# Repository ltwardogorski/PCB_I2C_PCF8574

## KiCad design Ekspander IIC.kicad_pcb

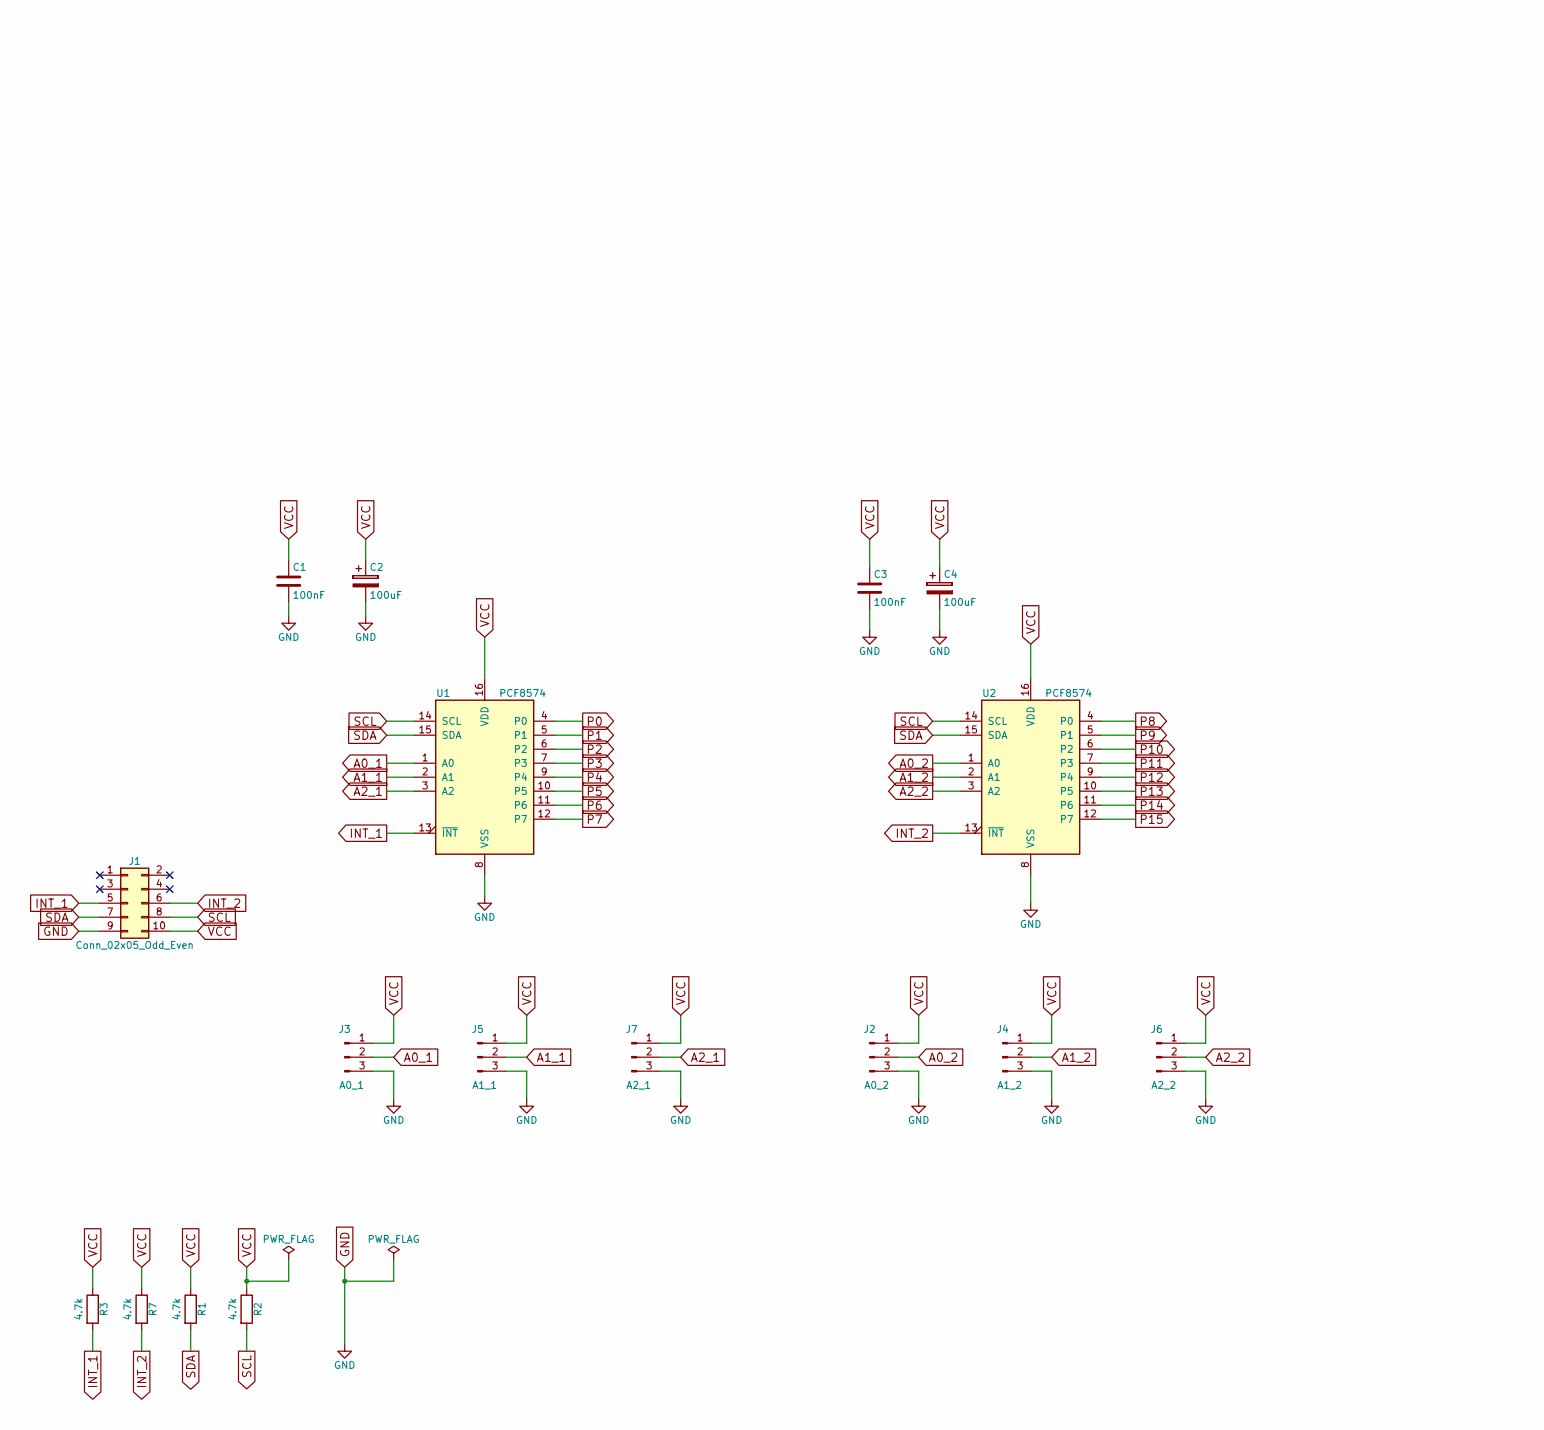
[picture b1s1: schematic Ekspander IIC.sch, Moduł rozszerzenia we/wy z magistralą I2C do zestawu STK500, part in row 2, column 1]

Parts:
C1, C3: 100nF; C_0805
C2, C4: 100uF; CP_Elec_8x6.5
J1: Conn_02x05_Odd_Even; Pin_Header_Straight_2x05_Pitch2.54mm
J2: A0_2; Pin_Header_Straight_1x03_Pitch2.54mm
J3: A0_1; Pin_Header_Straight_1x03_Pitch2.54mm
J4: A1_2; Pin_Header_Straight_1x03_Pitch2.54mm
J5: A1_1; Pin_Header_Straight_1x03_Pitch2.54mm
J6: A2_2; Pin_Header_Straight_1x03_Pitch2.54mm
J7: A2_1; Pin_Header_Straight_1x03_Pitch2.54mm
R1, R2, R3, R7: 4.7k; R_0805
U1, U2: PCF8574; DIP-16_W7.62mm

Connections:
A0_1: J3.2, U1.1 (A0)
A0_2: J2.2, U2.1 (A0)
A1_1: J5.2, U1.2 (A1)
A1_2: J4.2, U2.2 (A1)
A2_1: J7.2, U1.3 (A2)
A2_2: J6.2, U2.3 (A2)
GND: C1.2, C2.2, C3.2, C4.2, J1.9, J2.3, J3.3, J4.3, J5.3, J6.3, J7.3, U1.8 (VSS), U2.8 (VSS); also elsewhere on the board
INT_1: J1.5, R3.2, U1.13 (~INT~)
INT_2: J1.6, R7.2, U2.13 (~INT~)
P0: U1.4 (P0); also elsewhere on the board
P1: U1.5 (P1); also elsewhere on the board
P2: U1.6 (P2); also elsewhere on the board
P3: U1.7 (P3); also elsewhere on the board
P4: U1.9 (P4); also elsewhere on the board
P5: U1.10 (P5); also elsewhere on the board
P6: U1.11 (P6); also elsewhere on the board
P7: U1.12 (P7); also elsewhere on the board
P8: U2.4 (P0); also elsewhere on the board
P9: U2.5 (P1); also elsewhere on the board
P10: U2.6 (P2); also elsewhere on the board
P11: U2.7 (P3); also elsewhere on the board
P12: U2.9 (P4); also elsewhere on the board
P13: U2.10 (P5); also elsewhere on the board
P14: U2.11 (P6); also elsewhere on the board
P15: U2.12 (P7); also elsewhere on the board
SCL: J1.8, R2.2, U1.14 (SCL), U2.14 (SCL); also elsewhere on the board
SDA: J1.7, R1.2, U1.15 (SDA), U2.15 (SDA); also elsewhere on the board
VCC: C1.1, C2.1, C3.1, C4.1, J1.10, J2.1, J3.1, J4.1, J5.1, J6.1, J7.1, R1.1, R2.1, R3.1, R7.1, U1.16 (VDD), U2.16 (VDD); also elsewhere on the board

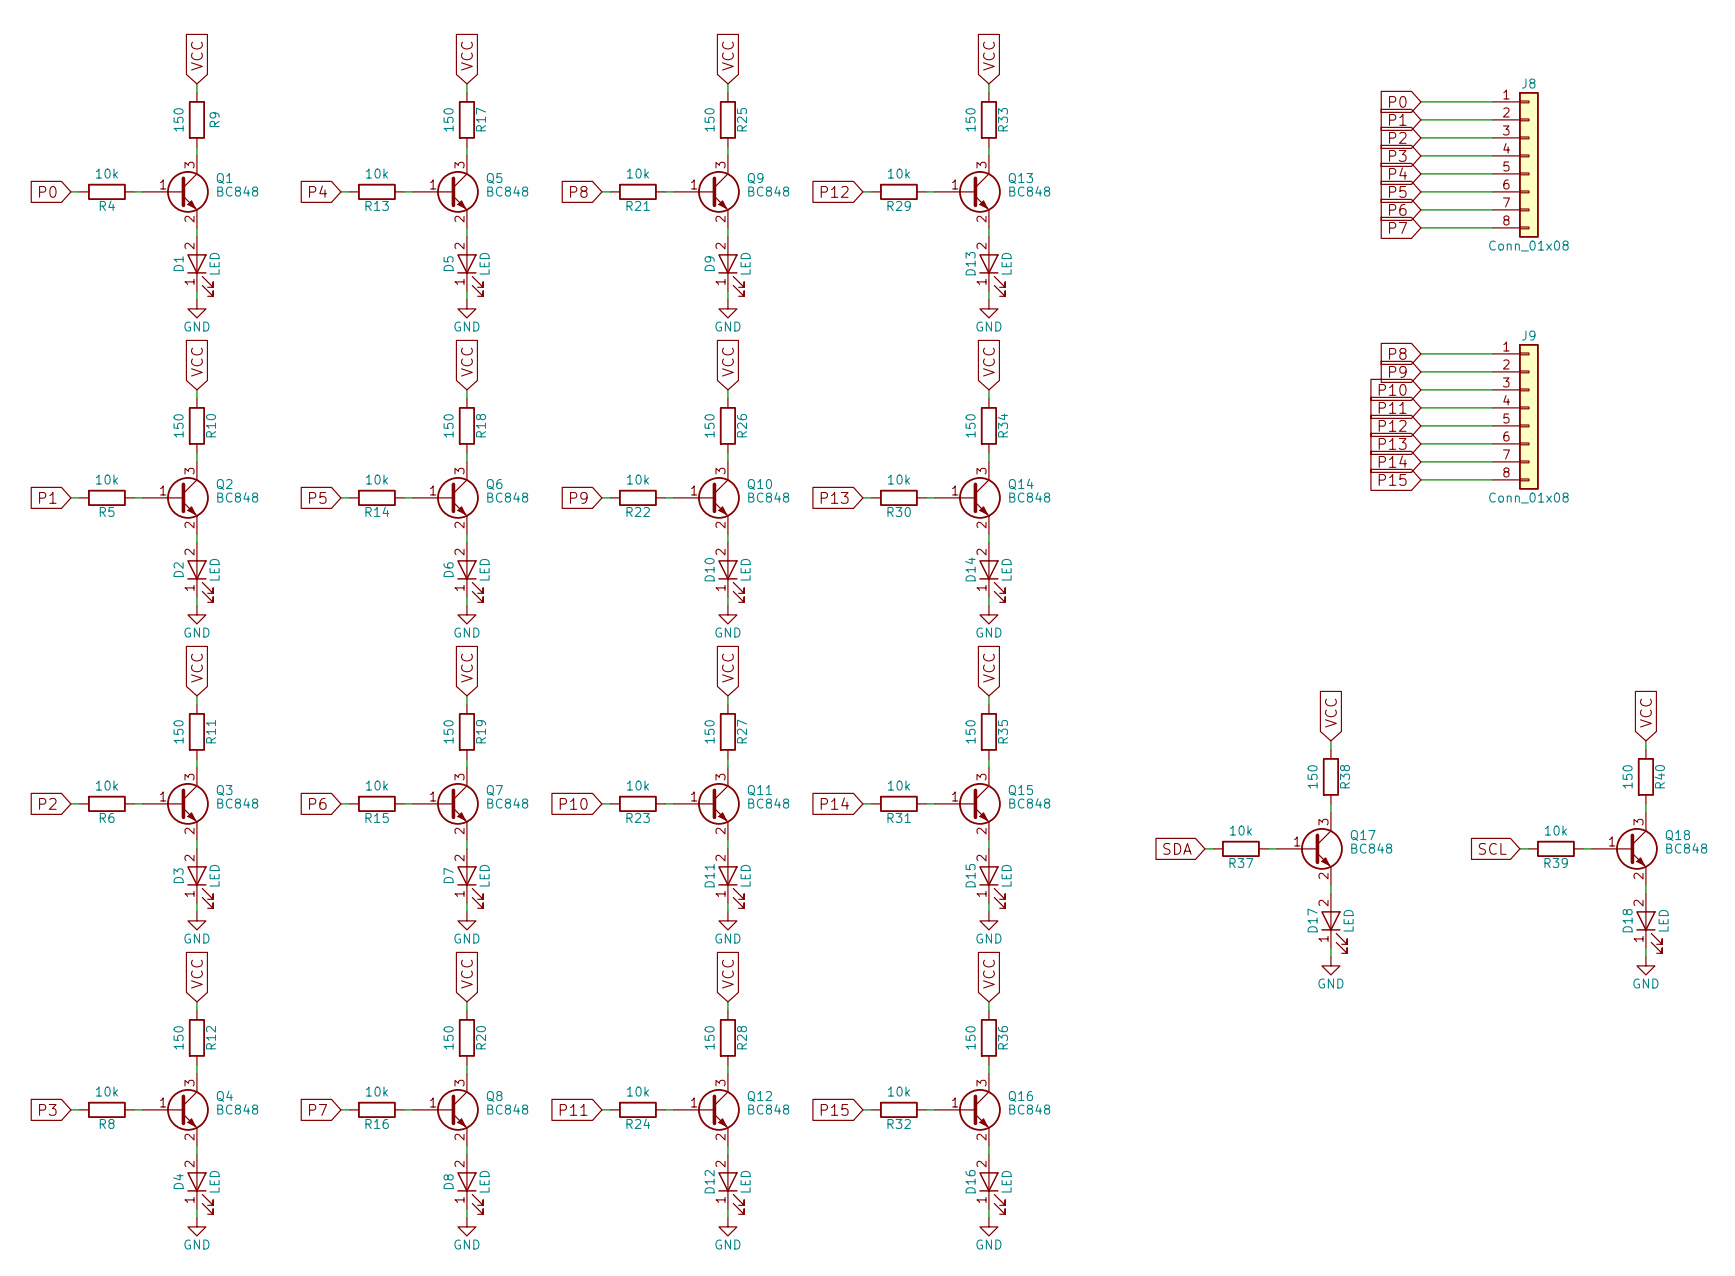
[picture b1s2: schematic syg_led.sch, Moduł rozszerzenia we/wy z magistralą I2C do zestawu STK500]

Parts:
D1, D2, D3, D4, D5, D6, D7, D8, D9, D10, D11, D12, D13, D14, D15, D16, D17, D18: LED; LED_1206
J8, J9: Conn_01x08; Pin_Header_Straight_1x08_Pitch2.54mm
Q1, Q2, Q3, Q4, Q5, Q6, Q7, Q8, Q9, Q10, Q11, Q12, Q13, Q14, Q15, Q16, Q17, Q18: BC848; SOT-23
R4, R5, R6, R8, R13, R14, R15, R16, R21, R22, R23, R24, R29, R30, R31, R32, R37, R39: 10k; R_0805
R9, R10, R11, R12, R17, R18, R19, R20, R25, R26, R27, R28, R33, R34, R35, R36, R38, R40: 150; R_0805

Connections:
GND: D1.1 (K), D2.1 (K), D3.1 (K), D4.1 (K), D5.1 (K), D6.1 (K), D7.1 (K), D8.1 (K), D9.1 (K), D10.1 (K), D11.1 (K), D12.1 (K), D13.1 (K), D14.1 (K), D15.1 (K), D16.1 (K), D17.1 (K), D18.1 (K); also elsewhere on the board
unnamed: D1.2 (A), Q1.2 (E)
unnamed: D2.2 (A), Q2.2 (E)
unnamed: D3.2 (A), Q3.2 (E)
unnamed: D4.2 (A), Q4.2 (E)
unnamed: D5.2 (A), Q5.2 (E)
unnamed: D6.2 (A), Q6.2 (E)
unnamed: D7.2 (A), Q7.2 (E)
unnamed: D8.2 (A), Q8.2 (E)
unnamed: D9.2 (A), Q9.2 (E)
unnamed: D10.2 (A), Q10.2 (E)
unnamed: D11.2 (A), Q11.2 (E)
unnamed: D12.2 (A), Q12.2 (E)
unnamed: D13.2 (A), Q13.2 (E)
unnamed: D14.2 (A), Q14.2 (E)
unnamed: D15.2 (A), Q15.2 (E)
unnamed: D16.2 (A), Q16.2 (E)
unnamed: D17.2 (A), Q17.2 (E)
unnamed: D18.2 (A), Q18.2 (E)
unnamed: Q1.1 (B), R4.1
unnamed: Q1.3 (C), R9.2
unnamed: Q2.1 (B), R5.1
unnamed: Q2.3 (C), R10.2
unnamed: Q3.1 (B), R6.1
unnamed: Q3.3 (C), R11.2
unnamed: Q4.1 (B), R8.1
unnamed: Q4.3 (C), R12.2
unnamed: Q5.1 (B), R13.1
unnamed: Q5.3 (C), R17.2
unnamed: Q6.1 (B), R14.1
unnamed: Q6.3 (C), R18.2
unnamed: Q7.1 (B), R15.1
unnamed: Q7.3 (C), R19.2
unnamed: Q8.1 (B), R16.1
unnamed: Q8.3 (C), R20.2
unnamed: Q9.1 (B), R21.1
unnamed: Q9.3 (C), R25.2
unnamed: Q10.1 (B), R22.1
unnamed: Q10.3 (C), R26.2
unnamed: Q11.1 (B), R23.1
unnamed: Q11.3 (C), R27.2
unnamed: Q12.1 (B), R24.1
unnamed: Q12.3 (C), R28.2
unnamed: Q13.1 (B), R29.1
unnamed: Q13.3 (C), R33.2
unnamed: Q14.1 (B), R30.1
unnamed: Q14.3 (C), R34.2
unnamed: Q15.1 (B), R31.1
unnamed: Q15.3 (C), R35.2
unnamed: Q16.1 (B), R32.1
unnamed: Q16.3 (C), R36.2
unnamed: Q17.1 (B), R37.1
unnamed: Q17.3 (C), R38.2
unnamed: Q18.1 (B), R39.1
unnamed: Q18.3 (C), R40.2
P0: J8.1, R4.2; also elsewhere on the board
P1: J8.2, R5.2; also elsewhere on the board
P2: J8.3, R6.2; also elsewhere on the board
P3: J8.4, R8.2; also elsewhere on the board
P4: J8.5, R13.2; also elsewhere on the board
P5: J8.6, R14.2; also elsewhere on the board
P6: J8.7, R15.2; also elsewhere on the board
P7: J8.8, R16.2; also elsewhere on the board
P8: J9.1, R21.2; also elsewhere on the board
P9: J9.2, R22.2; also elsewhere on the board
P10: J9.3, R23.2; also elsewhere on the board
P11: J9.4, R24.2; also elsewhere on the board
P12: J9.5, R29.2; also elsewhere on the board
P13: J9.6, R30.2; also elsewhere on the board
P14: J9.7, R31.2; also elsewhere on the board
P15: J9.8, R32.2; also elsewhere on the board
SCL: R39.2; also elsewhere on the board
SDA: R37.2; also elsewhere on the board
VCC: R9.1, R10.1, R11.1, R12.1, R17.1, R18.1, R19.1, R20.1, R25.1, R26.1, R27.1, R28.1, R33.1, R34.1, R35.1, R36.1, R38.1, R40.1; also elsewhere on the board

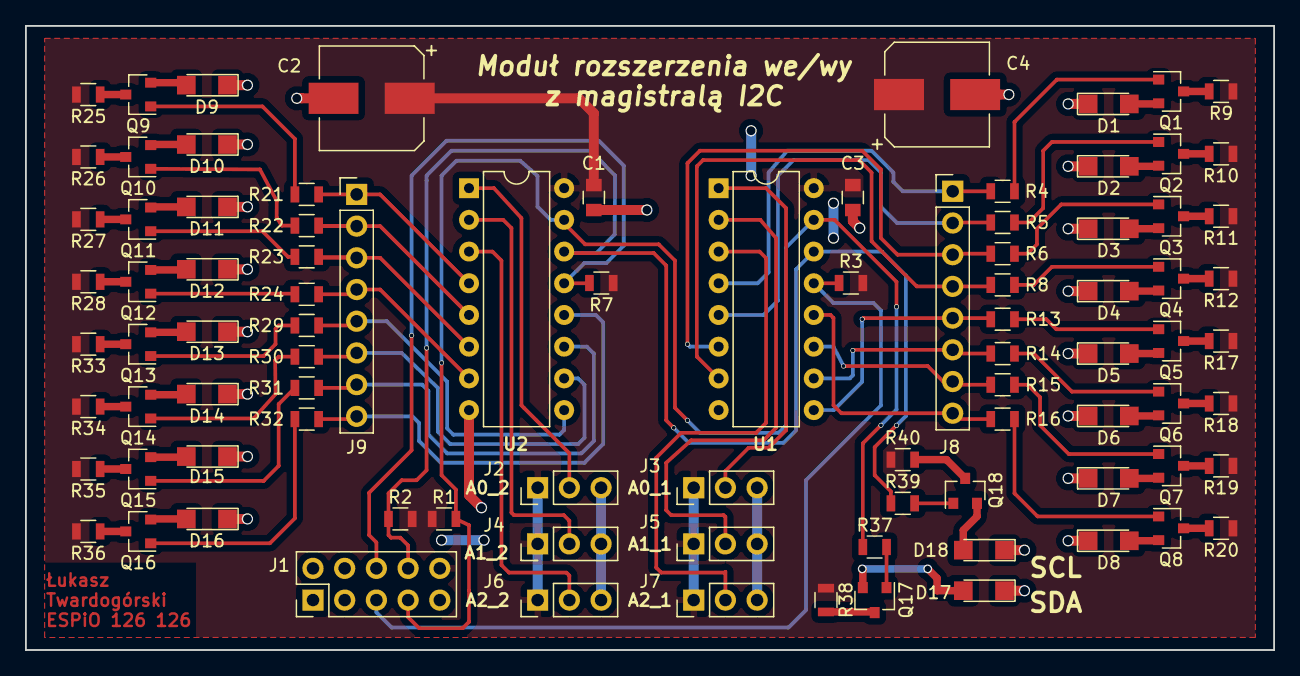
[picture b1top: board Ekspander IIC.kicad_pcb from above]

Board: 2 copper layers, 100.0 x 50.0 mm, 91 parts (0 on the bottom side), 82 nets.

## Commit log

2018-10-29 final_project
